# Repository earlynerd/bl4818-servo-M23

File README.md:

# BL4818 Brushless Servo Musical Actuator

This repository contains the electronics, embedded firmware, host software,
and browser players for a network of brushless servo percussion actuators.
The actuators use modified BL4818 motor-controller hardware, a Nuvoton M2003
microcontroller, hall sensing, and an MT6701 absolute encoder to move a mallet
with controlled timing and force.

The system is in active use: roughly 35 actuators have been built, and the
firmware plus MIDI player/server are working well. The software is much closer
to production-ready than the replication documentation, so this repository
should currently be treated as a proven project under documentation rather
than a turn-key kit.

## Watch

check out video of these actuators playing various instruments on [my Instagram!](www.instagram.com/sly.vester)

Each self-contained actuator packages the modified BL4818 motor controller,
absolute encoder, power/data interface, and mallet mechanism inside the printed
shell. RX and TX connectors allow power and serial data to continue through the
actuator chain, while the recessed SWD port provides programming access.

## System overview

```mermaid
flowchart LR
    MIDI["MIDI file or browser player"] --> HTTP["Python MIDI server"]
    HTTP --> IFACE["USB serial / interface hardware"]
    IFACE --> A0["Actuator 0"]
    A0 --> A1["Actuator 1"]
    A1 --> AN["More actuators"]
    AN --> IFACE
```

The Python server owns the serial port and serves the browser UI. It enumerates
the actuator ring, maps MIDI pitches to actuator addresses, schedules strikes,
compensates for measured mechanical latency, and can build then deploy APROM
updates through the permanent LDROM loaders without releasing the serial port.
The updater and synchronized chord scheduler are hardware-validated on the
14-actuator handpan ring.
Each actuator closes its own
current, velocity, and position loops and runs the homing/strike state machine.
The current protocol uses a four-bit address and supports up to 16 actuators per
ring.

## What is in this repository

- `src/` and `include/`: M2003 bare-metal firmware.
- `scripts/`: ring-bus client, MIDI server, tuning, measurement, and demo tools.
- `player/`: browser-based MIDI player, looper, and tongue-drum player.
- `pcb/`: KiCad electronics plus current mechanical/fabrication exports.
- `mechanical/`: SolidWorks source CAD and STEP exports for the actuator shell,
  mallet holder, and interface-board reference model.
- `docs/`: replication notes, hardware references, debug history, and design notes.
- `protocol.md`: byte-level Ring Bus Protocol v2 specification.
- `midi_server_api.md`: HTTP API for integrations and custom players.

See [Repository map](docs/repository-map.md) for a guided tour.

## Quick software start

The firmware builds on Windows and POSIX hosts, including Raspbian. Its Makefile
expects GNU Make and the Arm GNU toolchain in `PATH`. Initial SWD provisioning
still uses the PowerShell/J-Link scripts and is therefore Windows-oriented.

### 1. Install host dependencies

Install Python 3.10 or newer, then from the repository root run:

```powershell
py -m venv .venv
.\.venv\Scripts\Activate.ps1
py -m pip install -r requirements.txt
```

### 2. Build the firmware

Install `arm-none-eabi-gcc` and GNU Make, then run:

```powershell
make
```

The main output is `build/m2003-motor.bin`. Generate the complete J-Link
payload (application, commit manifest, permanent LDROM loader, and read-only
CONFIG capture) with:

```powershell
powershell -File scripts/build-jlink.ps1
```

Generation does not contact hardware or change CONFIG. The stable Gen1 ring
updater, its recovery evidence, and its completed 14-actuator validation are
documented in [Ring firmware update](docs/firmware-update.md). The LDROM loader
is now maintenance-only; no further Gen1 loader features are planned.

### 3. Flash an actuator

Connect the programmer over SWD and run:

```powershell
powershell -File scripts/flash-jlink.ps1
```

For J-Link V9.58 or newer, use the faster native M2003FC1AE flash loader:

```powershell
powershell -ExecutionPolicy Bypass -File scripts/flash-jlink.ps1 -NativeFlash
```

Add `-SkipBuild` to reuse the generated artifacts, or `-GenerateOnly` to build
them without contacting hardware. Native mode retains the CONFIG preservation,
commit-last manifest, and physical verification described below. Omitting
`-NativeFlash` retains the original per-word programming method.

This standard command first records CONFIG0..2, programs and byte-verifies
APROM, its manifest, and LDROM, then preserves the existing configuration while
selecting LDROM-first boot. It refuses automatic CONFIG changes on a locked or
unexpected security configuration. Disconnect motor power while changing
wiring or attaching the programmer; a servo actuator can move unexpectedly
during bring-up.

### 4. Start the MIDI player

Connect the interface serial port to a powered actuator ring and run:

```powershell
py scripts/ring_midi_server.py -p COM7 --library-dir C:\path\to\midi-library
```

Open <http://localhost:8765/>. Enumerate the ring, home the actuators, and assign
a MIDI pitch to each slot before playing a file. Use the instrument selector
to save and switch named pitch maps and player settings. Profiles are stored locally in
`instruments.json` and are intentionally not committed. An existing
`mapping.json` is imported as the Default profile.

For multiple rings, use one USB adapter per ring (at most 16 actuators each):

```powershell
py scripts/ring_midi_server.py --ring jameson=COM29,10 --ring retuned=COM48,10
```

The player provides a saved-instrument selector for each ring and shared playback
controls. See [multiple-ring setup](docs/host-software.md#multiple-rings-on-one-server)
for profile persistence and slot routing. The Firmware panel lets you select
rings to update and processes them one after another.

For a first hardware check without the browser:

```powershell
py scripts/ring_tool.py -p COM7 enumerate
py scripts/ring_tool.py -p COM7 status 0
```

Run `py scripts/ring_tool.py --help` for the complete command list.

## Documentation

- [Replication guide](docs/replication-guide.md): staged path from hardware to a playing ring.
- [Hardware guide](docs/hardware.md): current BL4818 modification and actuator assembly architecture.
- [Performance video](docs/video/handpan_video_h264.mp4): ten actuators playing with sound.
- [Firmware guide](docs/firmware.md): architecture, build, flash, and module boundaries.
- [Ring firmware update](docs/firmware-update.md): stable LDROM recovery design, flash layout, operation, and validation record.
- [Host software guide](docs/host-software.md): server, browser players, and bench tools.
- [Replication status](docs/replication-status.md): what is reproducible now and what still needs source material.
- [Ring Bus Protocol v2](protocol.md): serial packet and command specification.
- [MIDI server HTTP API](midi_server_api.md): integration API.
- [Design decisions](Decisions.md) and [debug log](DebugLog.md): engineering history.

## Replication status and safety

The repository does not yet contain enough verified information for a new
builder to safely reproduce the complete actuator without assistance. In
particular, power-system limits, connector pinouts, a released BOM, mechanical
assembly dimensions, and a photographed bring-up procedure still need to be
documented. Those gaps are tracked explicitly in
[Replication status](docs/replication-status.md); unknown values are not guessed
in the guides.

This project drives a fast moving mechanism at several amps. Use a current-
limited supply during bring-up, keep hands and instruments clear of the mallet,
provide a physical power disconnect, and test one actuator before assembling a
ring.

## License

No project-wide license has been selected yet. Until one is added, the source
is visible for evaluation but normal open-source reuse permissions have not
been granted. A license should be chosen before presenting the repository as a
fully replicable open-source project; third-party code under `CMSIS/`,
`Library/`, and `RTT/` retains its own notices and terms.

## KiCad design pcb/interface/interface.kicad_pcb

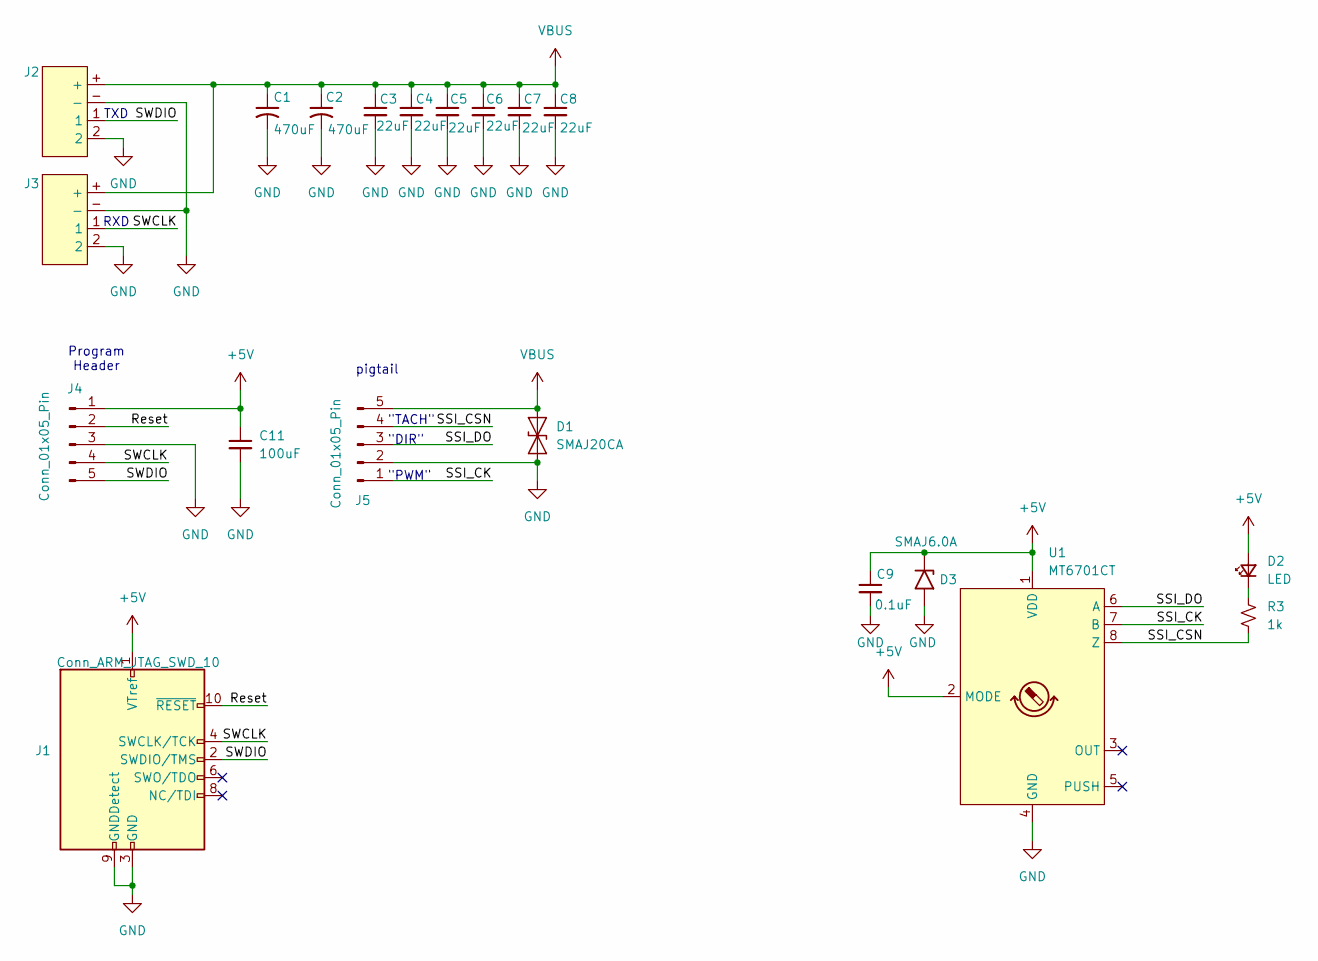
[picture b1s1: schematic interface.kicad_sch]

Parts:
C1, C2: 470uF; C_Radial_D8.0mm_H7.0mm_P3.50mm
C3, C4, C5, C6, C7, C8: 22uF; C_0805_2012Metric
C9: 0.1uF; C_0603_1608Metric
C11: 100uF; C_1206_3216Metric
D1: SMAJ20CA; D_SMA
D2: LED; LED_0603_1608Metric
D3: SMAJ6.0A; D_SMA
J1: Conn_ARM_JTAG_SWD_10; PinHeader_2x05_P1.27mm_Vertical_SMD
J2, J3: XT30(2+2)PB-M.G.B
J4, J5: Conn_01x05_Pin; JST_PH_B5B-PH-K_1x05_P2.00mm_Vertical
R3: 1k; R_0603_1608Metric
U1: MT6701CT; SO-8_3.9x4.9mm_P1.27mm

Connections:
+5V: C9.1, C11.1, D2.2 (A), D3.1 (A1), J1.1 (VTref), J4.1, U1.1 (VDD), U1.2 (MODE)
/Reset: J1.10 (~RESET), J4.2
/SSI_CK: J5.1, U1.7 (B)
/SSI_CSN: J5.4, R3.2, U1.8 (Z)
/SSI_DO: J5.3, U1.6 (A)
/SWCLK: J1.4 (SWCLK/TCK), J3.1, J4.4
/SWDIO: J1.2 (SWDIO/TMS), J2.1, J4.5
GND: C1.2, C2.2, C3.2, C4.2, C5.2, C6.2, C7.2, C8.2, C9.2, C11.2, D1.1 (A1), D3.2 (A2), J1.3 (GND), J1.5 (GND), J1.9 (GNDDetect), J2.2, J2.-, J3.2, J3.-, J4.3, J5.2, U1.4 (GND)
unnamed: D2.1 (K), R3.1
VBUS: C1.1, C2.1, C3.1, C4.1, C5.1, C6.1, C7.1, C8.1, D1.2 (A2), J2.+, J3.+, J5.5

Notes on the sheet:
RXD
pigtail
"TACH"
Program Header
"PWM"
"DIR"
TXD

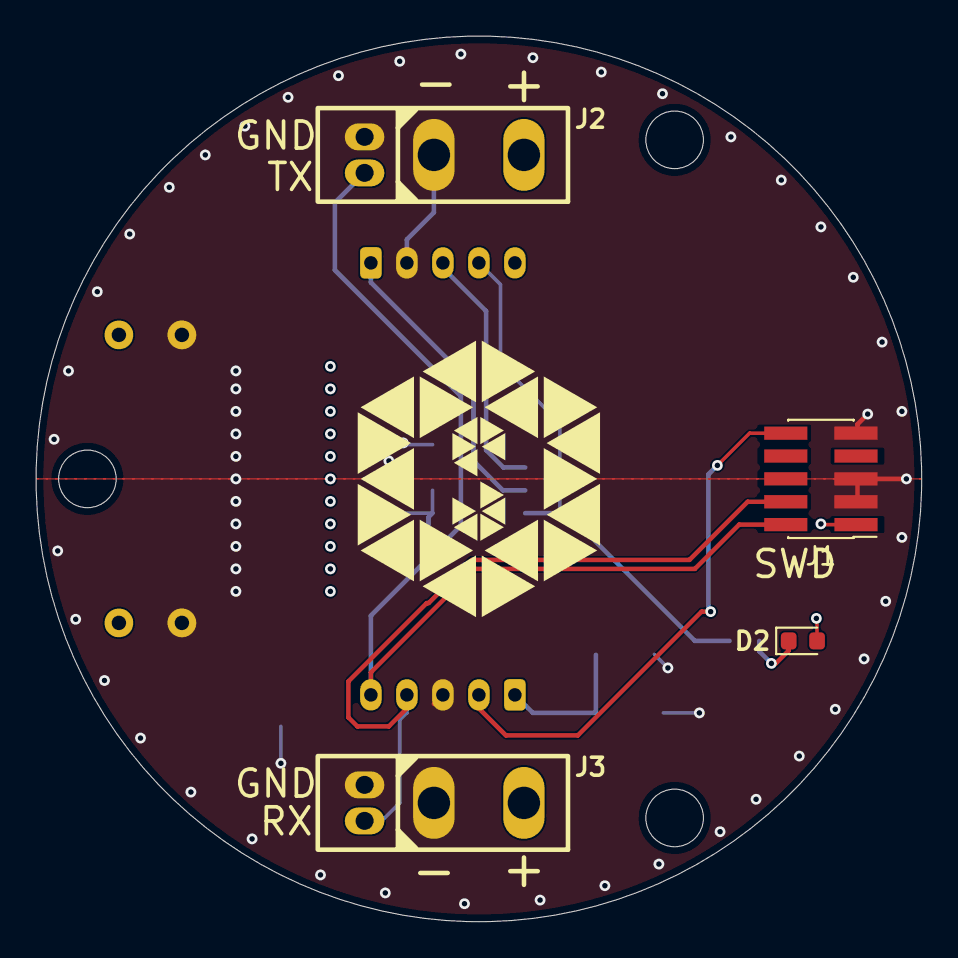
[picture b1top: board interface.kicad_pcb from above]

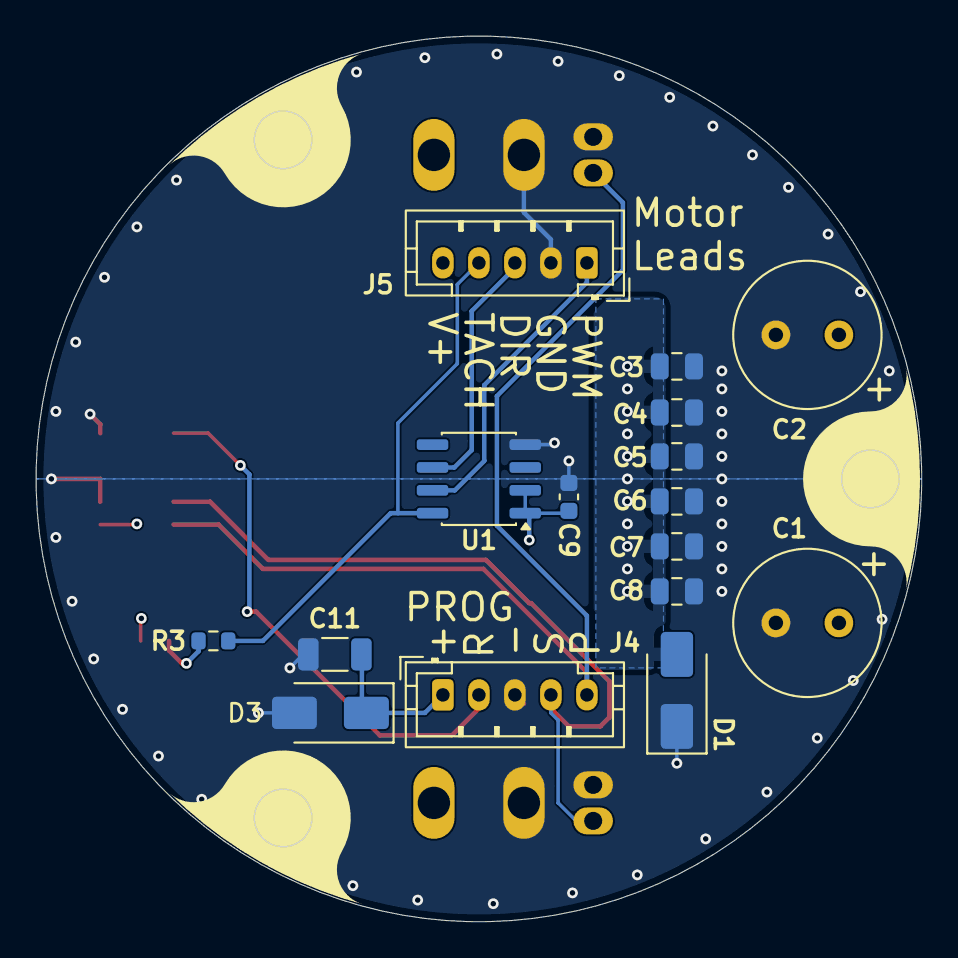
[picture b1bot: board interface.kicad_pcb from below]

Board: 4 copper layers, 49.2 x 49.2 mm, 20 parts (16 on the bottom side), 10 nets.

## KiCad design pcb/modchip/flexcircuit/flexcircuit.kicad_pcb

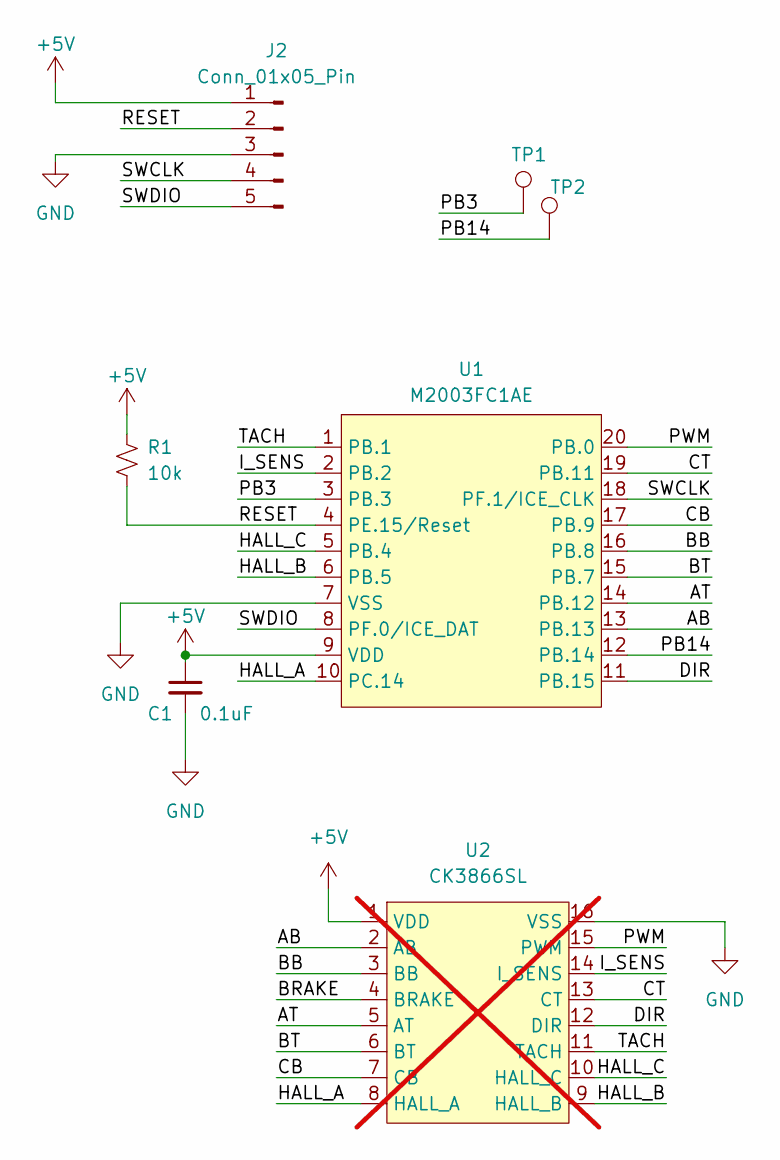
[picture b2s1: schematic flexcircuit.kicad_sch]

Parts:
C1: 0.1uF; C_0603_1608Metric
J2: Conn_01x05_Pin; JST_PH_B5B-PH-SM4-TB_1x05-1MP_P2.00mm_Vertical
R1: 10k; R_0603_1608Metric
TP1, TP2: TestPoint; TestPoint_Pad_D2.0mm
U1: M2003FC1AE; TSSOP-20_4.4x6.5mm_P0.65mm
U2: CK3866SL; SOIC-16_3.9x9.9mm_P1.27mm; not fitted

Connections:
+5V: C1.1, J2.1, R1.1, U1.9 (VDD), U2.1 (VDD)
/AB: U1.13 (PB.13), U2.2 (AB)
/AT: U1.14 (PB.12), U2.5 (AT)
/BB: U1.16 (PB.8), U2.3 (BB)
/BRAKE: U2.4 (BRAKE)
/BT: U1.15 (PB.7), U2.6 (BT)
/CB: U1.17 (PB.9), U2.7 (CB)
/CT: U1.19 (PB.11), U2.13 (CT)
/DIR: U1.11 (PB.15), U2.12 (DIR)
/HALL_A: U1.10 (PC.14), U2.8 (HALL_A)
/HALL_B: U1.6 (PB.5), U2.9 (HALL_B)
/HALL_C: U1.5 (PB.4), U2.10 (HALL_C)
/I_SENS: U1.2 (PB.2), U2.14 (I_SENS)
/PB3: TP1.1, U1.3 (PB.3)
/PB14: TP2.1, U1.12 (PB.14)
/PWM: U1.20 (PB.0), U2.15 (PWM)
/RESET: J2.2, R1.2, U1.4 (PE.15/Reset)
/SWCLK: J2.4, U1.18 (PF.1/ICE_CLK)
/SWDIO: J2.5, U1.8 (PF.0/ICE_DAT)
/TACH: U1.1 (PB.1), U2.11 (TACH)
GND: C1.2, J2.3, U1.7 (VSS), U2.16 (VSS)

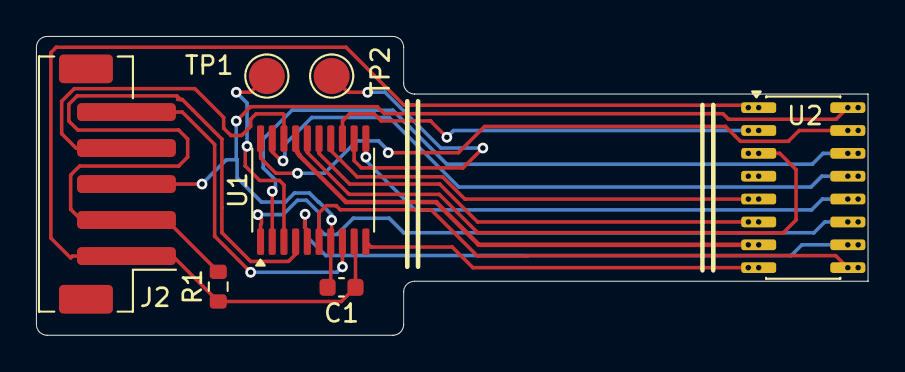
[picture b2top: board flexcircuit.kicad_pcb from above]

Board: 2 copper layers, 46.2 x 16.6 mm, 7 parts (0 on the bottom side), 20 nets.

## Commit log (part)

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2026-04-04 port to m2003 mcu
2026-04-05 encoder and commutation and protocol 2
2026-04-05 velocity loop
2026-04-06 position loop
2026-04-06 32 bit data types
2026-04-06 fix direction change bug
    commutation updates immediately when commanded duty sign changes
2026-04-06 mallet strike
2026-04-06 adc oversampling
    and fix stale naming
2026-04-07 persistent parameter store
2026-04-08 update protocol with response type
2026-04-09 strike timing and pcb
2026-04-09 pcb dev
2026-04-10 calibration artifacts
2026-04-11 midi player beginnings
2026-04-12 current loop
2026-04-12 interrupt based commutation
2026-04-13 interface PCB layout
2026-04-13 loop timing adjustment
2026-04-14 drop counters
2026-04-14 interposer board
2026-04-14 code review
2026-04-14 flex circuit as ordered
2026-04-14 timing diagnostics
2026-04-16 fix reversed connector
    and add a TVS diode
2026-04-18 BOD, adc and encoder faults
2026-04-18 adc priority
2026-04-18 clearer pcb labeling
2026-04-18 drumbeat test script
2026-04-23 indicators and scripts
2026-04-30 midi server
2026-04-30 player fixes
2026-05-01 encoder polarity detection
2026-05-06 midi player piano roll update
2026-05-06 timing info responses
2026-05-08 timing compensation
2026-05-10 looper
2026-05-13 persistent mapping
2026-05-13 midi library
2026-05-13 save to library
2026-05-13 mallet color pallete
2026-05-20 better binning
2026-05-23 API documentation
2026-05-25 API example
2026-05-25 as-ordered V2 interface boards
2026-05-27 midi player api example
2026-05-28 server side scheduling
2026-05-29 FIX server timing reporting
2026-06-04 indicator polarity and arpeggio
2026-06-04 ring bus timing error counts
2026-06-09 network scan server
2026-06-15 deadstrike and better library browser
